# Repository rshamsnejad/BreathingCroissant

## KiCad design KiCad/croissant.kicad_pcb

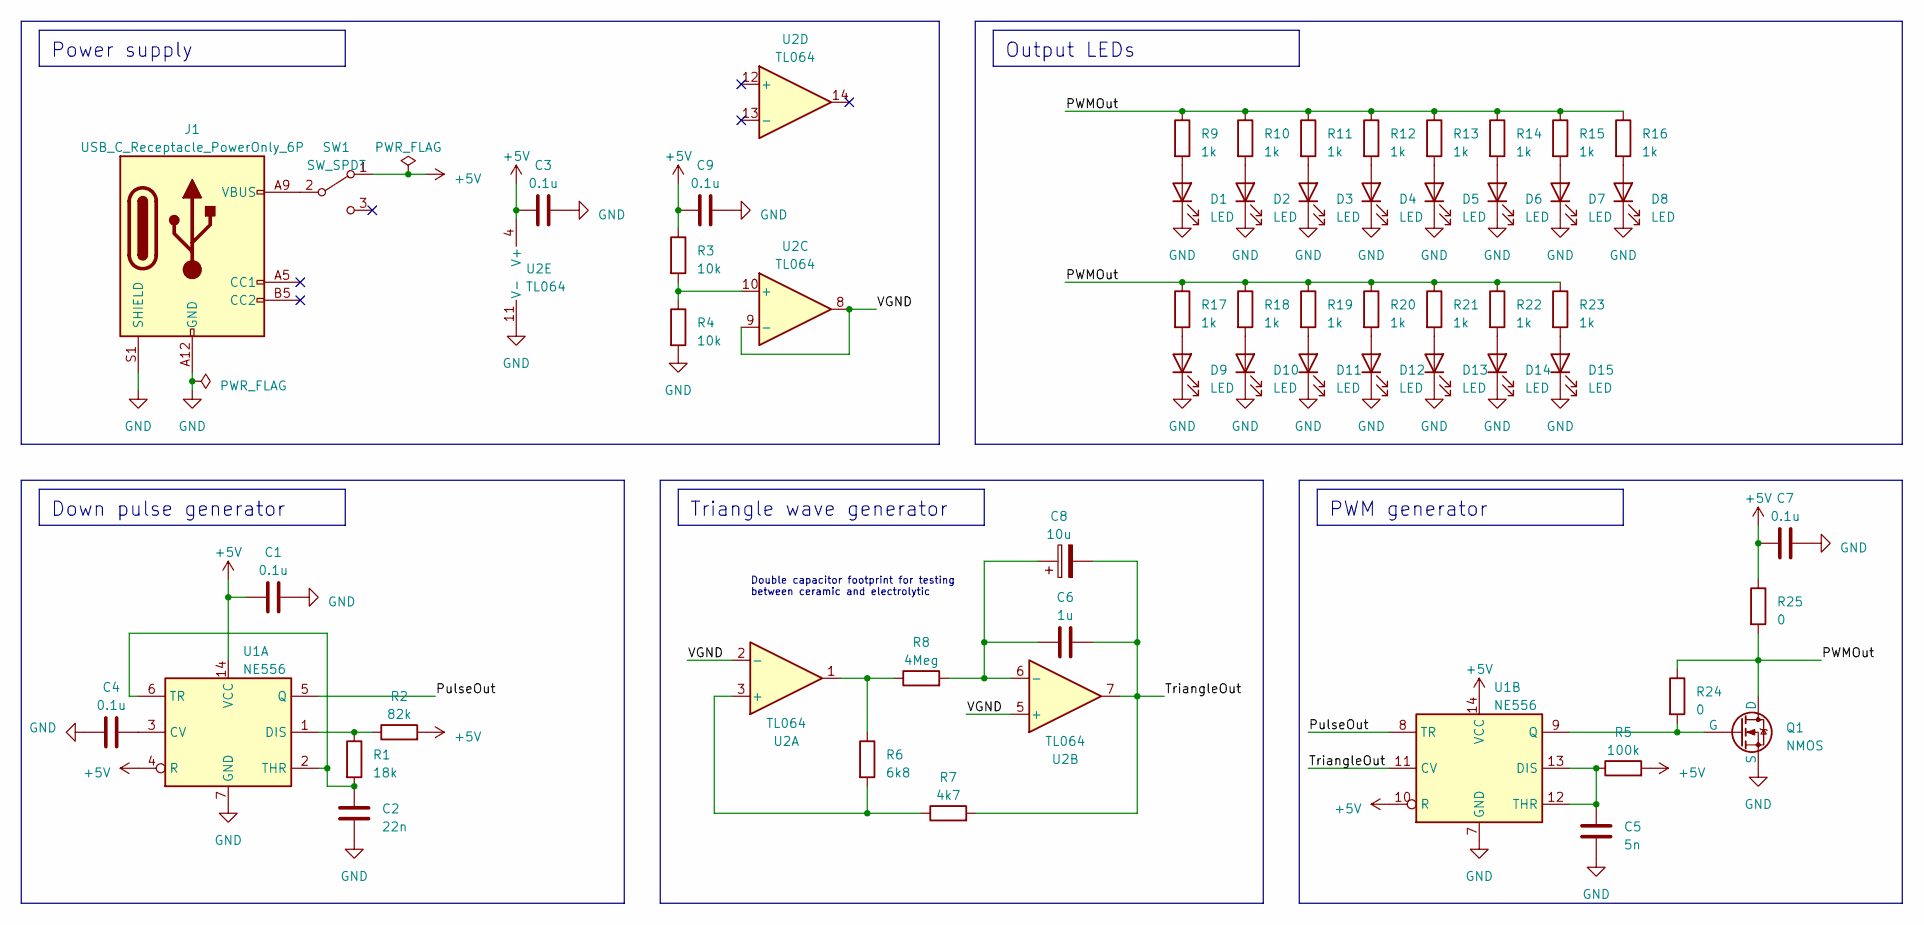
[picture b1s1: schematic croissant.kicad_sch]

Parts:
C1, C3, C4, C7, C9: 0.1u; C_0603_1608Metric
C2: 22n; C_0603_1608Metric
C5: 5n; C_0603_1608Metric
C6: 1u; C_0603_1608Metric
C8: 10u; CP_Elec_4x3
D1, D2, D3, D4, D5, D6, D7, D8, D9, D10, D11, D12, D13, D14, D15: LED; LED_0603_NOSILK
J1: USB_C_Receptacle_PowerOnly_6P; USB_C_Receptacle_GCT_USB4135-GF-A_6P_TopMnt_Horizontal
Q1: NMOS; SOT-23
R1: 18k; R_0603_1608Metric
R2: 82k; R_0603_1608Metric
R3, R4: 10k; R_0603_1608Metric
R5: 100k; R_0603_1608Metric
R6: 6k8; R_0603_1608Metric
R7: 4k7; R_0603_1608Metric
R8: 4Meg; R_0603_1608Metric
R9, R10, R11, R12, R13, R14, R15, R16, R17, R18, R19, R20, R21, R22, R23: 1k; R_0603_1608Metric
R24, R25: 0; R_0603_1608Metric
SW1: SW_SPDT; JS102011JCQN
U1: NE556; SOIC-14_3.9x8.7mm_P1.27mm
U2: TL064; SOIC-14_3.9x8.7mm_P1.27mm

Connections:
+5V: C1.1, C3.1, C7.1, C9.1, R2.2, R3.1, R5.2, R25.1, SW1.1 (A), U1.4 (R), U1.10 (R), U1.14 (VCC), U2.4 (V+)
/PWMOut: Q1.1 (D), R9.1, R10.1, R11.1, R12.1, R13.1, R14.1, R15.1, R16.1, R17.1, R18.1, R19.1, R20.1, R21.1, R22.1, R23.1, R24.1, R25.2
/PulseOut: U1.5 (Q), U1.8 (TR)
/TriangleOut: C6.2, C8.2, R7.2, U1.11 (CV), U2.7
/VGND: U2.2 (-), U2.5 (+), U2.8, U2.9 (-)
GND: C1.2, C2.1, C3.2, C4.1, C5.1, C7.2, C9.2, D1.1 (K), D2.1 (K), D3.1 (K), D4.1 (K), D5.1 (K), D6.1 (K), D7.1 (K), D8.1 (K), D9.1 (K), D10.1 (K), D11.1 (K), D12.1 (K), D13.1 (K), D14.1 (K), D15.1 (K), J1.A12 (GND), J1.B12 (GND), J1.S1 (SHIELD), Q1.3 (S), R4.2, U1.7 (GND), U2.11 (V-)
unnamed: D1.2 (A), R9.2
unnamed: D2.2 (A), R10.2
unnamed: D3.2 (A), R11.2
unnamed: D4.2 (A), R12.2
unnamed: D5.2 (A), R13.2
unnamed: D6.2 (A), R14.2
unnamed: D7.2 (A), R15.2
unnamed: D8.2 (A), R16.2
unnamed: D9.2 (A), R17.2
unnamed: D10.2 (A), R18.2
unnamed: D11.2 (A), R19.2
unnamed: D12.2 (A), R20.2
unnamed: D13.2 (A), R21.2
unnamed: D14.2 (A), R22.2
unnamed: D15.2 (A), R23.2
unnamed: Q1.2 (G), R24.2, U1.9 (Q)
unnamed: R6.1, R8.1, U2.1
unnamed: J1.A9 (VBUS), J1.B9 (VBUS), SW1.2 (B)
unnamed: C4.2, U1.3 (CV)
unnamed: R1.1, R2.1, U1.1 (DIS)
unnamed: C2.2, R1.2, U1.2 (THR), U1.6 (TR)
unnamed: C5.2, R5.1, U1.12 (THR), U1.13 (DIS)
unnamed: R6.2, R7.1, U2.3 (+)
unnamed: C6.1, C8.1, R8.2, U2.6 (-)
unnamed: R3.2, R4.1, U2.10 (+)

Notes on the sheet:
Power supply
Down pulse generator
Output LEDs
PWM generator
Triangle wave generator
Double capacitor footprint for testing between ceramic and electrolytic

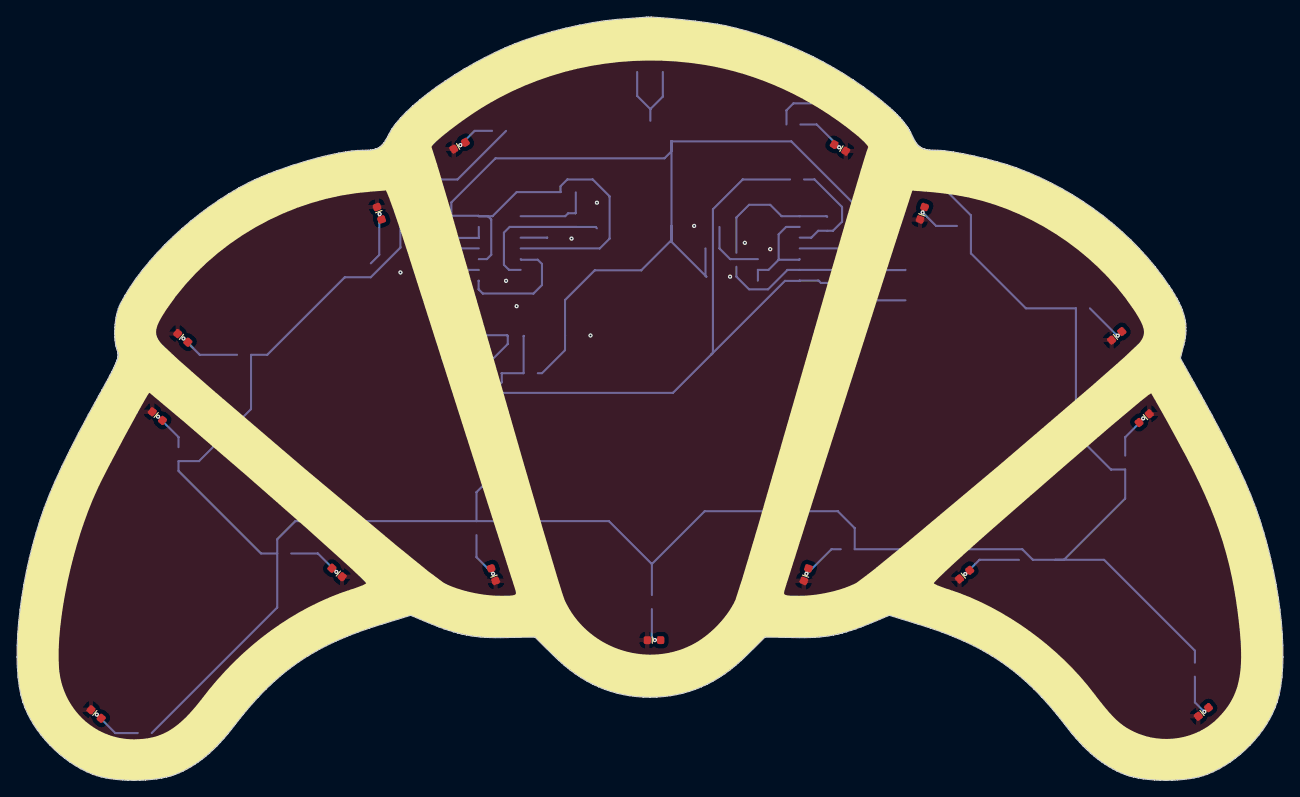
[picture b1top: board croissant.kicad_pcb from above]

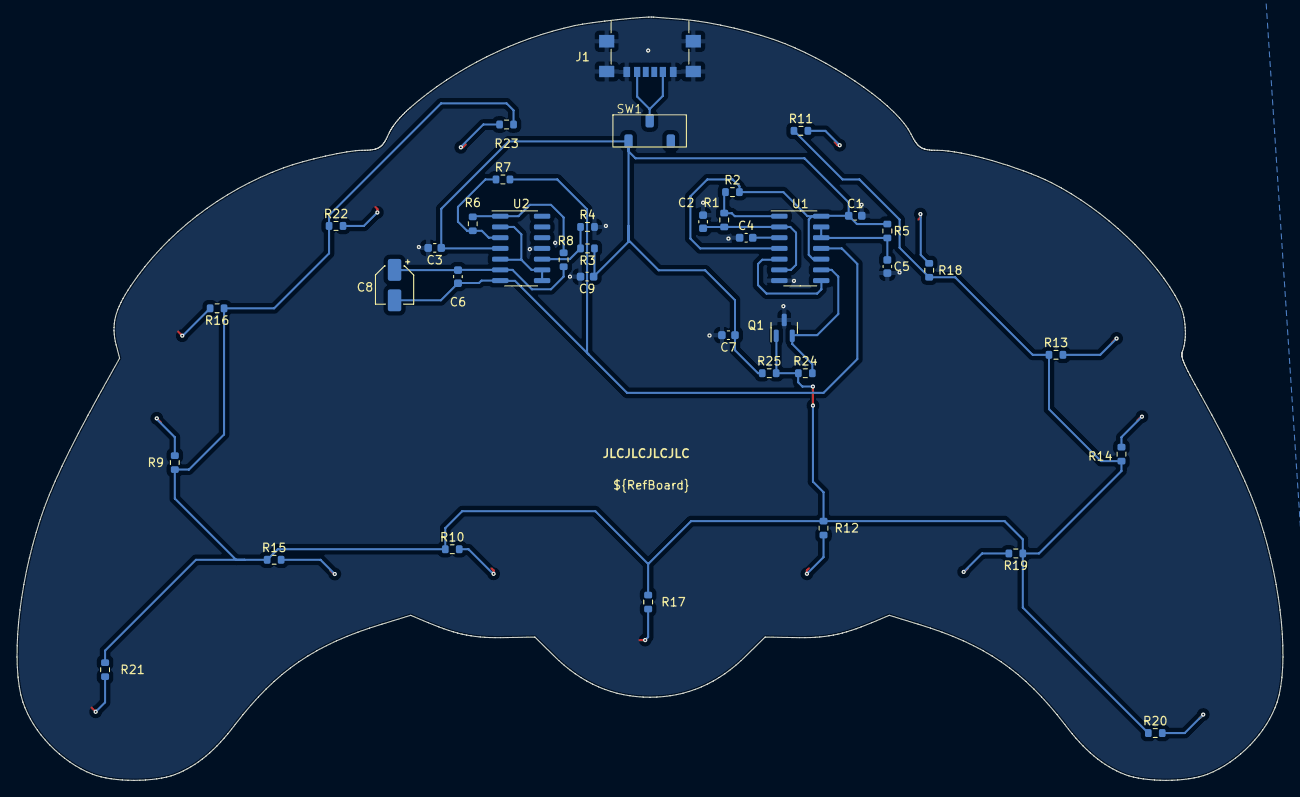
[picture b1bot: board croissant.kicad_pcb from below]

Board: 2 copper layers, 149.8 x 90.3 mm, 54 parts (39 on the bottom side), 31 nets.

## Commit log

2023-02-15 Add first files
2023-02-15 Fix parts
2023-02-15 Switch pulse generation to 2nd 555
2023-02-15 Add ShopCart
2023-02-16 Add oscillator
2023-02-16 Update gitignore
2023-02-17 Add working triangle oscillator
2023-02-17 Add osc to sim
2023-02-17 Working physical design (sim to be tweaked)
2023-02-17 Switch to TL062
2023-02-17 Fix cap value
2023-02-18 Fix oscillator frequency
2023-02-19 Add Kicad schematic
2023-02-19 Update sim
2023-02-20 Add board outline
2023-02-20 Switch to TL064
2023-02-20 Add LEDs
2023-02-20 Fix opamp orientation
2023-02-20 Add LED driving transistor
2023-02-20 Specify component values
2023-02-20 Fix designator
2023-02-20 Add footprints
2023-02-20 Fix ERC
2023-02-20 Fix footprints
2023-02-20 Lower sim frequency
2023-02-20 Lower frequency
2023-02-20 Add second cap footprint
2023-02-20 Change SPST to SPDT
2023-02-20 Add SPDT footprint
2023-02-20 Fix JLCPCB stackup
2023-02-20 Advance routing
2023-02-20 Placed LEDs
2023-02-21 Fix via sizes
2023-02-21 Fix DRC for vias
2023-02-21 Fix LEDs silkscreen
2023-02-21 Finish layout
2023-02-21 Add JLC reference placeholder
2023-02-21 Add RefBoard on silkscreen
